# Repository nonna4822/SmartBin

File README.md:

# SmartBin
## โปรเจคนี้เป็นส่วนหนึ่งของรายวิชา Embedded System 
    เกี่ยวกับการทำ Smart device  โดยใช้ Atmega328p 
## อุปกรณ์ที่ใช้
* atmega328p
* PIR sensor
* Motor x 2
* Ultrasonic sensor 
## ความคืบหน้า
- [x] เปิดปิดถังขยะ / proteus
- [x] เปิดปิดถังขยะ / protoboard
- [x] เปิดปิดถังขยะ / ของจริง
##

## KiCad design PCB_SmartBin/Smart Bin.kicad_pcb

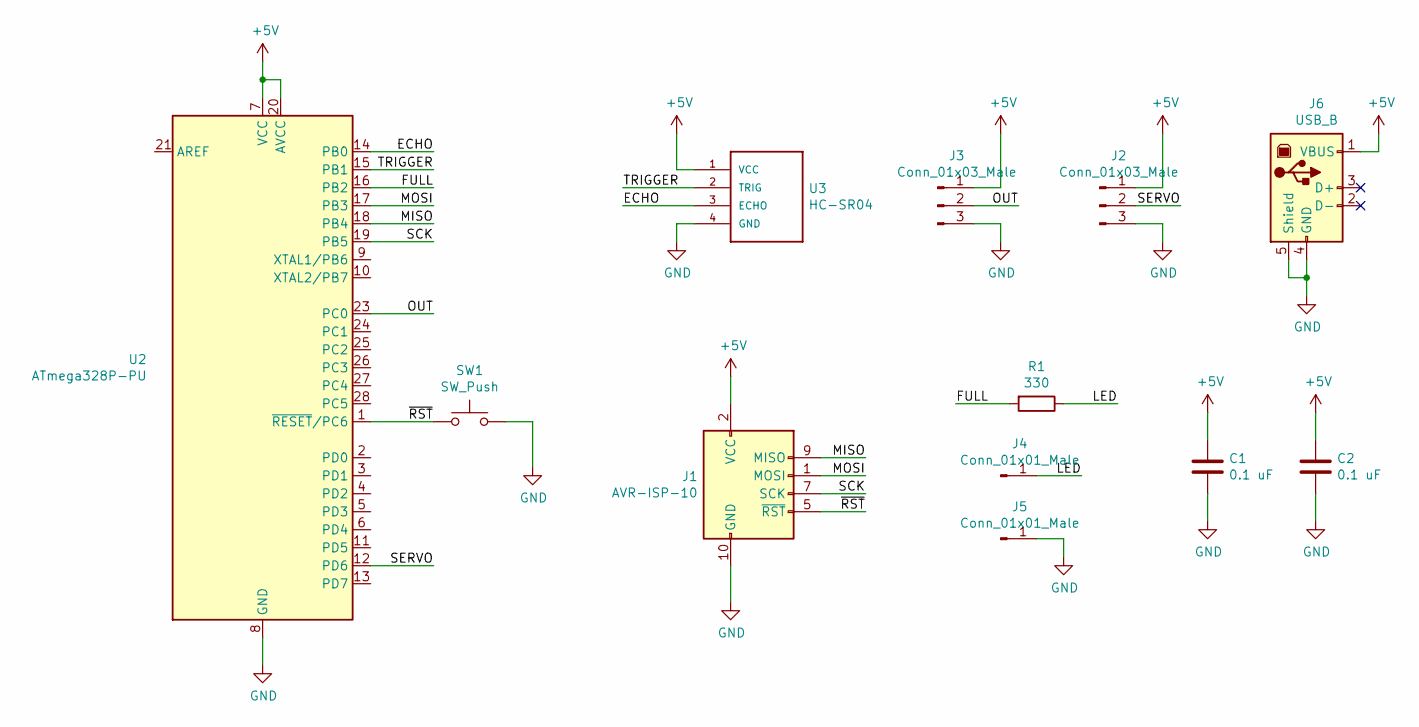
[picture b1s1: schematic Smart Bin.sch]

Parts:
C1, C2: 0.1 uF; C_Disc_D4.3mm_W1.9mm_P5.00mm
J1: AVR-ISP-10; PinHeader_2x05_P2.54mm_Vertical
J2, J3: Conn_01x03_Male; PinHeader_1x03_P2.54mm_Vertical
J4, J5: Conn_01x01_Male; PinHeader_1x01_P2.54mm_Vertical
J6: USB_B; USB_B_Amphenol_MUSB-D511_Vertical_Rugged
R1: 330; R_Axial_DIN0207_L6.3mm_D2.5mm_P10.16mm_Horizontal
SW1: SW_Push; SW_PUSH_6mm
U2: ATmega328P-PU; DIP-28_W7.62mm
U3: HC-SR04; XCVR_HC-SR04

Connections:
+5V: C1.1, C2.1, J1.2 (VCC), J2.1, J3.1, J6.1 (VBUS), U2.7 (VCC), U2.20 (AVCC), U3.1 (VCC)
/ECHO: U2.14 (PB0), U3.3 (ECHO)
/FULL: R1.2, U2.16 (PB2)
/LED: J4.1, R1.1
/MISO: J1.9 (MISO), U2.18 (PB4)
/MOSI: J1.1 (MOSI), U2.17 (PB3)
/OUT: J3.2, U2.23 (PC0)
/SCK: J1.7 (SCK), U2.19 (PB5)
/SERVO: J2.2, U2.12 (PD6)
/TRIGGER: U2.15 (PB1), U3.2 (TRIG)
/~RST: J1.5 (~RST), SW1.1, U2.1 (~RESET~/PC6)
GND: C1.2, C2.2, J1.4 (GND), J1.6 (GND), J1.8 (GND), J1.10 (GND), J2.3, J3.3, J5.1, J6.4 (GND), J6.5 (Shield), SW1.2, U2.8 (GND), U2.22 (GND), U3.4 (GND)

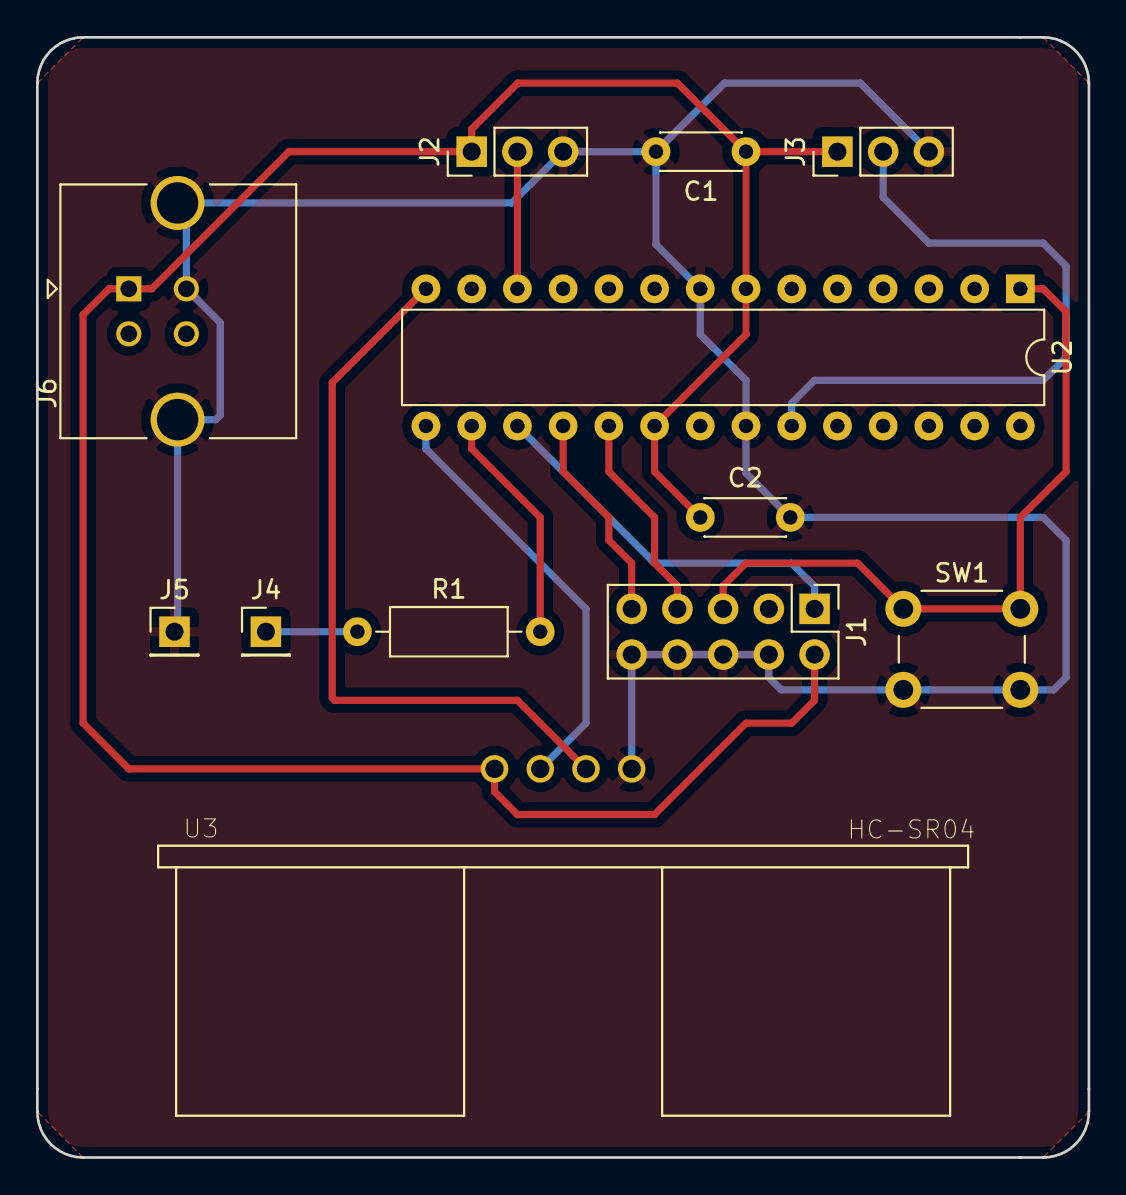
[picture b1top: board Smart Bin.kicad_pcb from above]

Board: 2 copper layers, 58.4 x 62.2 mm, 12 parts (0 on the bottom side), 12 nets.

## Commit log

2019-04-08 commit suthep pic for personal interested
2019-04-08 upload module
2019-04-08 add img
2019-04-17 add servo_motor file
2019-04-17 servo motor can rotate but only -90 to 90
2019-04-21 Finish servo motor
2019-04-21 Good bye niti
2019-04-21 byebye
2019-04-23 Finishhed
2019-04-23 Fish <3
2019-04-29 nara
2019-04-29 git add
2019-04-29 Revert "nara"
    This reverts commit f06be58127646fbd987ed24b186ccfcc1b291666.
2019-04-29 git merge
2019-04-29 commit new code
2019-04-30 timer0 is correct
2019-04-30 commit new
2019-04-30 add ignore
2019-04-30 add ultrasonic
2019-04-30 add ultrasonic function
2019-04-30 proteous all test
2019-04-30 back to less than 1
2019-04-30 what ...
2019-04-30 led yeah
2019-04-30 mix all together
2019-05-05 final code
